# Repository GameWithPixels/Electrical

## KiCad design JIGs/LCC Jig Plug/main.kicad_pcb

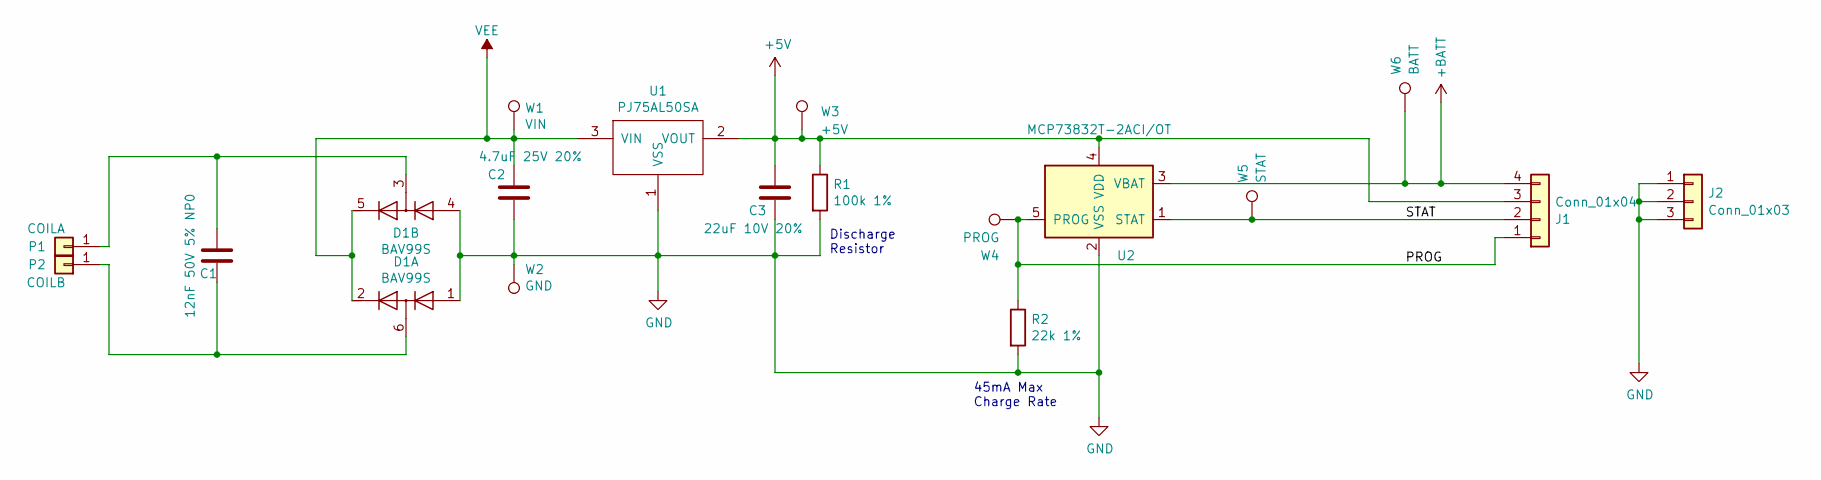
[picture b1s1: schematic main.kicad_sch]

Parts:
C1: 12nF 50V 5% NP0; C_0805_2012Metric; Manufacturer Part Number GRM2195C1H123JA01D; LCSC Part Number C97906
C2: 4.7uF 25V 20%; C_0603_1608Metric; Manufacturer Part Number GRM188R61E475KE11D; LCSC Part Number C90057
C3: 22uF 10V 20%; C_0603_1608Metric; Manufacturer Part Number GRM188R61A226ME15D; LCSC Part Number C84419
D1: BAV99S; SOT-363_SC-70-6; Manufacturer Part Number BAV99S,115; LCSC Part Number C96225
J1: Conn_01x04; PinHeader_1x04_P2.54mm_Vertical
J2: Conn_01x03; PinHeader_1x03_P2.54mm_Vertical
P1: COILA; TestPoint_THTPad_D1.5mm_Drill0.7mm
P2: COILB; TestPoint_THTPad_D1.5mm_Drill0.7mm
R1: 100k 1%; R_0402_1005Metric; Manufacturer Part Number 0402WGF1003TCE; LCSC Part Number C25741
R2: 22k 1%; R_0402_1005Metric; Manufacturer Part Number 0402WGF2202TCE; LCSC Part Number C25768
U1: PJ75AL50SA; SOT-23; Manufacturer Part Number PJ75AL50SA
U2: MCP73832T-2ACI/OT; SOT-23-5; Manufacturer Part Number MCP73832T-2ACI/OT; LCSC Part Number C38066
W1: VIN; TEST_PIN
W2: GND; TEST_PIN
W3: +5V; TEST_PIN
W4: PROG; TEST_PIN
W5: STAT; TEST_PIN
W6: BATT; TEST_PIN

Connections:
+5V: C3.1, J1.3, R1.1, U1.2 (VOUT), U2.4 (VDD), W3.1
+BATT: J1.4, U2.3 (VBAT), W6.1
/PROG: J1.1, R2.1, U2.5 (PROG), W4.1
/STAT: J1.2, U2.1 (STAT), W5.1
GND: C2.2, C3.2, D1.1 (A1), D1.4 (A3), J2.1, J2.2, J2.3, R1.2, R2.2, U1.1 (VSS), U2.2 (VSS), W2.1
unnamed: C1.2, D1.6 (K3A4), P2.1
unnamed: C1.1, D1.3 (K1A2), P1.1
VEE: C2.1, D1.2 (K2), D1.5 (K4), U1.3 (VIN), W1.1

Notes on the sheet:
Discharge Resistor
45mA Max Charge Rate

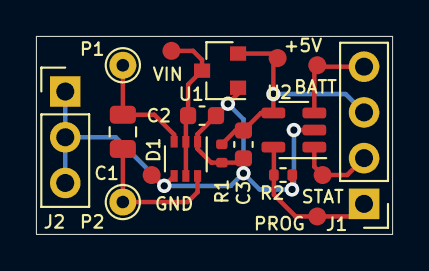
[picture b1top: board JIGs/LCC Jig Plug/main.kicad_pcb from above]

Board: 2 copper layers, 19.8 x 11.0 mm, 18 parts (0 on the bottom side), 8 nets.

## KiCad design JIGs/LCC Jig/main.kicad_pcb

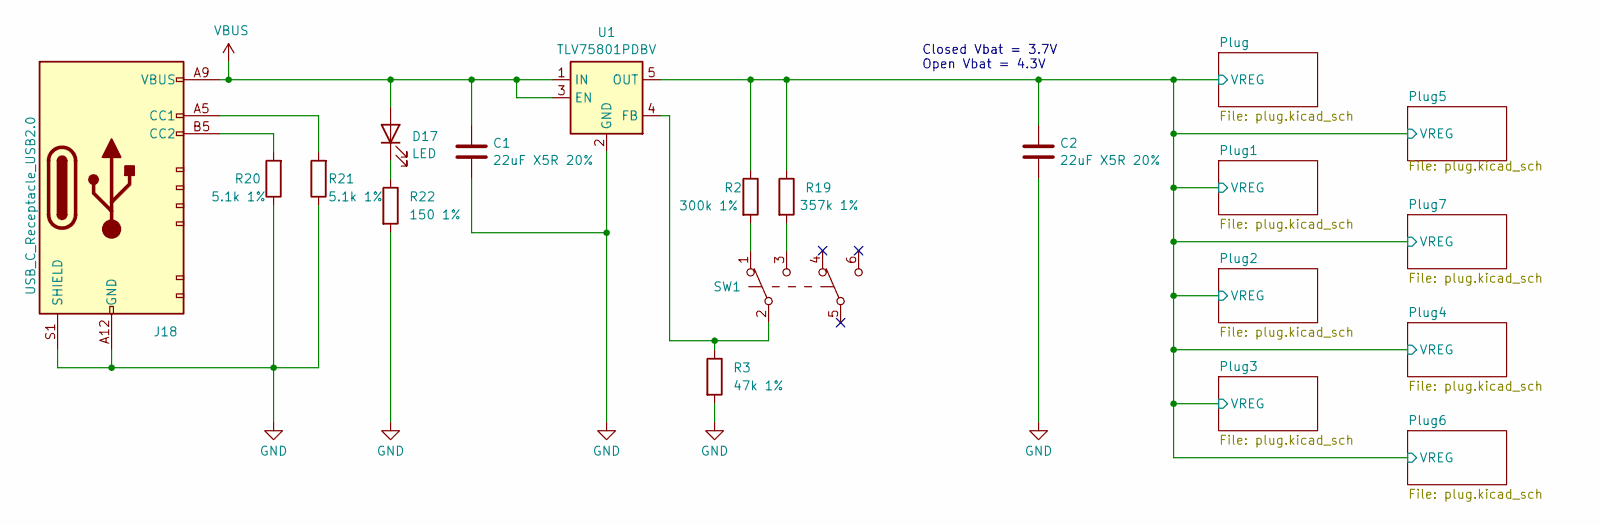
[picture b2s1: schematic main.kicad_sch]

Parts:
C1, C2: 22uF X5R 20%; C_0805_2012Metric; Part Number GRM21BR61E226ME44L; LCSC Part Number C86816
D17: LED; LED_0603_1608Metric; Part Number XL-1608UGC-04
J18: USB_C_Receptacle_USB2.0; USB-C-SMD_10P-P1.00-L6.8-W8.9; Part Number TYPE-C-31-M-17; LCSC Part Number C283540
R2: 300k 1%; R_0603_1608Metric; Part Number 0603WAF3003T5E
R3: 47k 1%; R_0603_1608Metric; Part Number 0603WAF4702T5E; LCSC Part Number C25819
R19: 357k 1%; R_0603_1608Metric; Part Number 0603WAF3573T5E
R20, R21: 5.1k 1%; R_0402_1005Metric; Part Number 0402WGF5101TCE; LCSC Part Number C25905
R22: 150 1%; R_0603_1608Metric; Part Number 0603WAF1500T5E; LCSC Part Number C22808
SW1: SW_Push_DPDT; XKB8080-W; Part Number XKB8080-W; LCSC Part Number C318861
U1: TLV75801PDBV; SOT-23-5; Part Number TLV75801PDBVR; LCSC Part Number C2877852

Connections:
/Plug/VREG: C2.1, R2.1, R19.1, U1.5 (OUT); also elsewhere on the board
GND: C1.2, C2.2, J18.A12 (GND), J18.B12 (GND), J18.S1 (SHIELD), R3.2, R20.1, R21.1, R22.2, U1.2 (GND); also elsewhere on the board
unnamed: D17.1 (K), R22.1
unnamed: J18.A5 (CC1), R21.2
unnamed: J18.B5 (CC2), R20.2
unnamed: R2.2, SW1.1 (A)
unnamed: R19.2, SW1.3 (C)
unnamed: R3.1, SW1.2 (B), U1.4 (FB)
VBUS: C1.1, D17.2 (A), J18.A9 (VBUS), J18.B9 (VBUS), U1.1 (IN), U1.3 (EN)

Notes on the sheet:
Closed Vbat = 3.7V Open Vbat = 4.3V

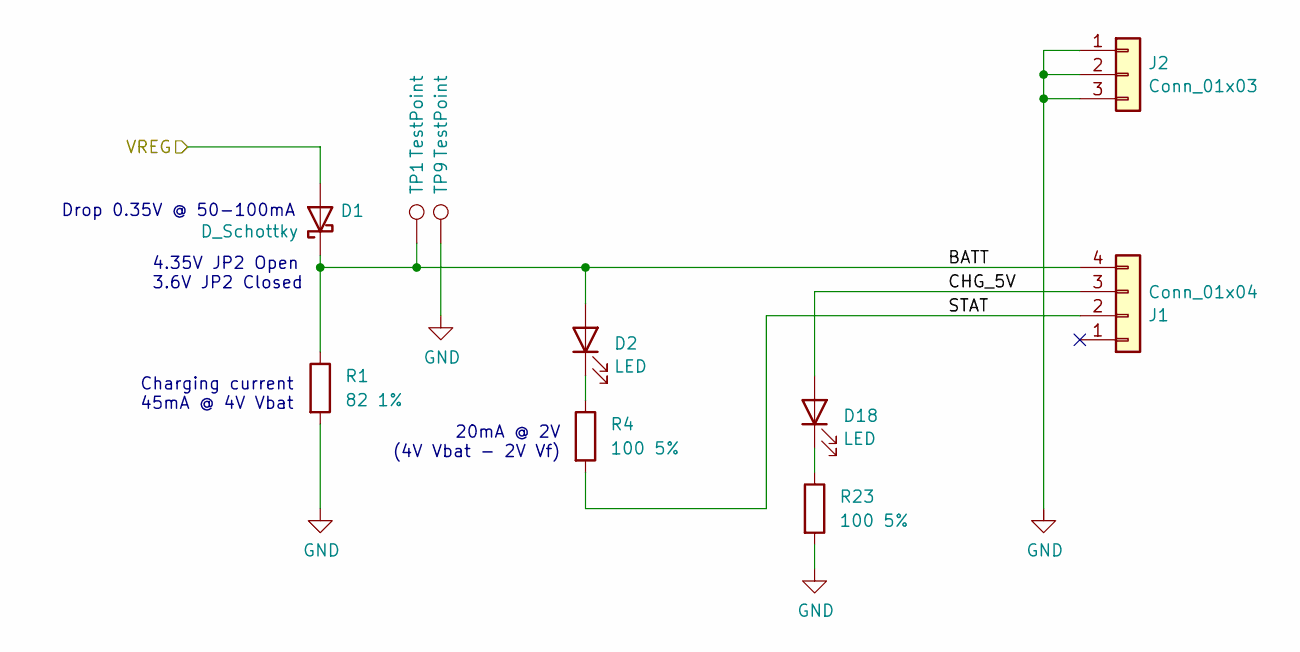
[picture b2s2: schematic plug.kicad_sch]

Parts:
D1: D_Schottky; D_SOD-523; Part Number RB521S30T1G; LCSC Part Number C145179
D2: LED; LED_0603_1608Metric; Part Number XL-1608SURC-06; LCSC Part Number C965799
D18: LED; LED_0603_1608Metric; Part Number XL-1608UOC-06
J1: Conn_01x04; PinSocket_1x04_P2.54mm_Vertical
J2: Conn_01x03; PinSocket_1x03_P2.54mm_Vertical
R1: 82 1%; R_1210_3225Metric; Part Number RC1210JR-0782RL; LCSC Part Number C728413
R4, R23: 100 5%; R_0603_1608Metric; Part Number 0603WAJ0101T5E; LCSC Part Number C25201
TP1, TP9: TestPoint; PinHeader_1x01_P2.54mm_Vertical

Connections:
/Plug/BATT: D1.1 (K), D2.2 (A), J1.4, R1.1, TP1.1
/Plug/CHG_5V: D18.2 (A), J1.3
/Plug/STAT: J1.2, R4.2
/Plug/VREG: D1.2 (A); also elsewhere on the board
GND: J2.1, J2.2, J2.3, R1.2, R23.2; also elsewhere on the board
unnamed: D2.1 (K), R4.1
unnamed: D18.1 (K), R23.1

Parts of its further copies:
D3, D5, D7, D9, D11, D13, D15: D_Schottky; D_SOD-523; Part Number RB521S30T1G; LCSC Part Number C145179
D4, D6, D8, D10, D12, D14, D16: LED; LED_0603_1608Metric; Part Number XL-1608SURC-06; LCSC Part Number C965799
D19, D20, D21, D22, D23, D24, D25: LED; LED_0603_1608Metric; Part Number XL-1608UOC-06
J3, J5, J7, J9, J11, J13, J15: Conn_01x04; PinSocket_1x04_P2.54mm_Vertical
J4, J6, J8, J10, J12, J14, J16: Conn_01x03; PinSocket_1x03_P2.54mm_Vertical
R5, R7, R9, R11, R13, R15, R17: 82 1%; R_1210_3225Metric; Part Number RC1210JR-0782RL; LCSC Part Number C728413
R6, R8, R10, R12, R14, R16, R18, R24, R25, R26, R27, R28, R29, R30: 100 5%; R_0603_1608Metric; Part Number 0603WAJ0101T5E; LCSC Part Number C25201
TP10: TestPoint; PinHeader_1x01_P2.54mm_Vertical

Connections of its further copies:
/Plug1/BATT: D3.1 (K), D4.2 (A), J3.4, R5.1
/Plug1/CHG_5V: D19.2 (A), J3.3
/Plug1/STAT: J3.2, R6.2
/Plug2/BATT: D5.1 (K), D6.2 (A), J5.4, R7.1
/Plug2/CHG_5V: D20.2 (A), J5.3
/Plug2/STAT: J5.2, R8.2
/Plug3/BATT: D7.1 (K), D8.2 (A), J7.4, R9.1
/Plug3/CHG_5V: D21.2 (A), J7.3
/Plug3/STAT: J7.2, R10.2
/Plug4/BATT: D13.1 (K), D14.2 (A), J13.4, R15.1
/Plug4/CHG_5V: D24.2 (A), J13.3
/Plug4/STAT: J13.2, R16.2
/Plug5/BATT: D9.1 (K), D10.2 (A), J9.4, R11.1
/Plug5/CHG_5V: D22.2 (A), J9.3
/Plug5/STAT: J9.2, R12.2
/Plug6/BATT: D15.1 (K), D16.2 (A), J15.4, R17.1
/Plug6/CHG_5V: D25.2 (A), J15.3
/Plug6/STAT: J15.2, R18.2
/Plug7/BATT: D11.1 (K), D12.2 (A), J11.4, R13.1
/Plug7/CHG_5V: D23.2 (A), J11.3
/Plug7/STAT: J11.2, R14.2
/Plug/VREG: D3.2 (A), D5.2 (A), D7.2 (A), D9.2 (A), D11.2 (A), D13.2 (A), D15.2 (A); also elsewhere on the board
GND: J4.1, J4.2, J4.3, J6.1, J6.2, J6.3, J8.1, J8.2, J8.3, J10.1, J10.2, J10.3, J12.1, J12.2, J12.3, J14.1, J14.2, J14.3, J16.1, J16.2, J16.3, R5.2, R7.2, R9.2, R11.2, R13.2, R15.2, R17.2, R24.2, R25.2, R26.2, R27.2, R28.2, R29.2, R30.2, TP10.1; also elsewhere on the board
unnamed: D4.1 (K), R6.1
unnamed: D6.1 (K), R8.1
unnamed: D8.1 (K), R10.1
unnamed: D10.1 (K), R12.1
unnamed: D12.1 (K), R14.1
unnamed: D14.1 (K), R16.1
unnamed: D16.1 (K), R18.1
unnamed: D19.1 (K), R24.1
unnamed: D20.1 (K), R25.1
unnamed: D21.1 (K), R26.1
unnamed: D22.1 (K), R27.1
unnamed: D23.1 (K), R28.1
unnamed: D24.1 (K), R29.1
unnamed: D25.1 (K), R30.1

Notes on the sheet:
20mA @ 2V (4V Vbat - 2V Vf)
4.35V JP2 Open 3.6V JP2 Closed
Charging current 45mA @ 4V Vbat
Drop 0.35V @ 50-100mA

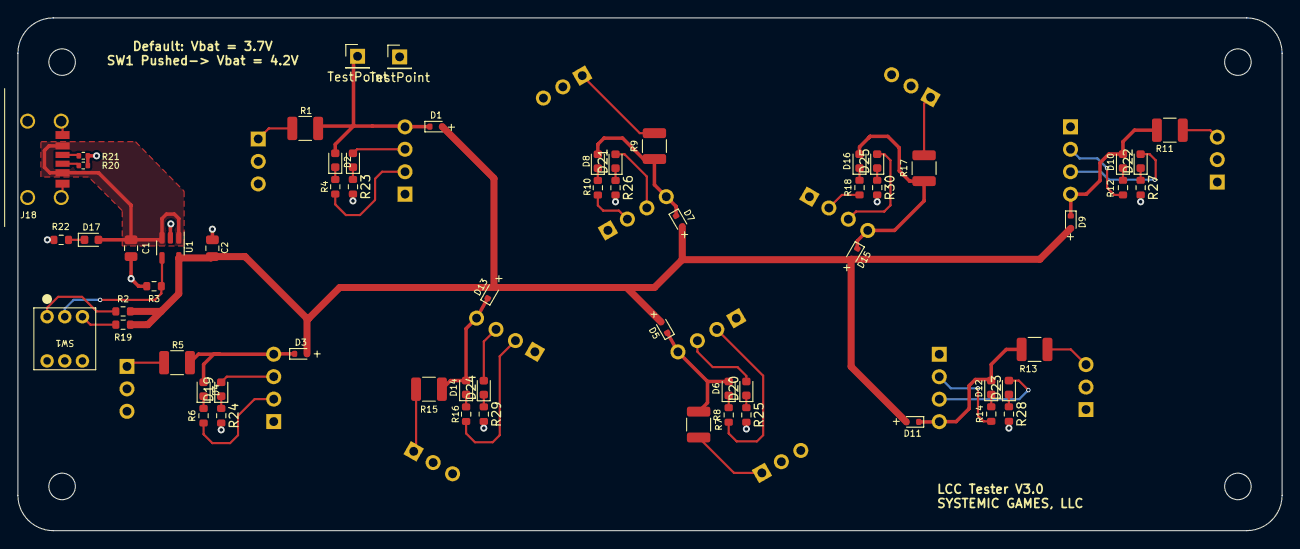
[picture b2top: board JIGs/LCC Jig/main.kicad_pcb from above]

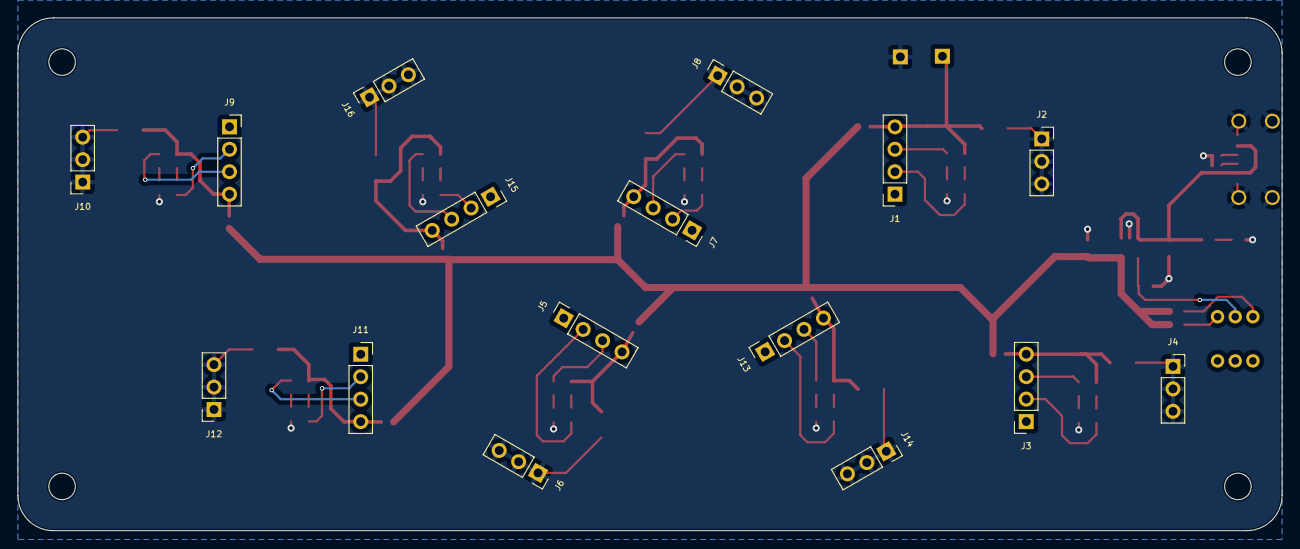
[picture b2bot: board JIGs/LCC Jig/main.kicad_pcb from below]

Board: 2 copper layers, 143.0 x 58.0 mm, 78 parts (16 on the bottom side), 49 nets.

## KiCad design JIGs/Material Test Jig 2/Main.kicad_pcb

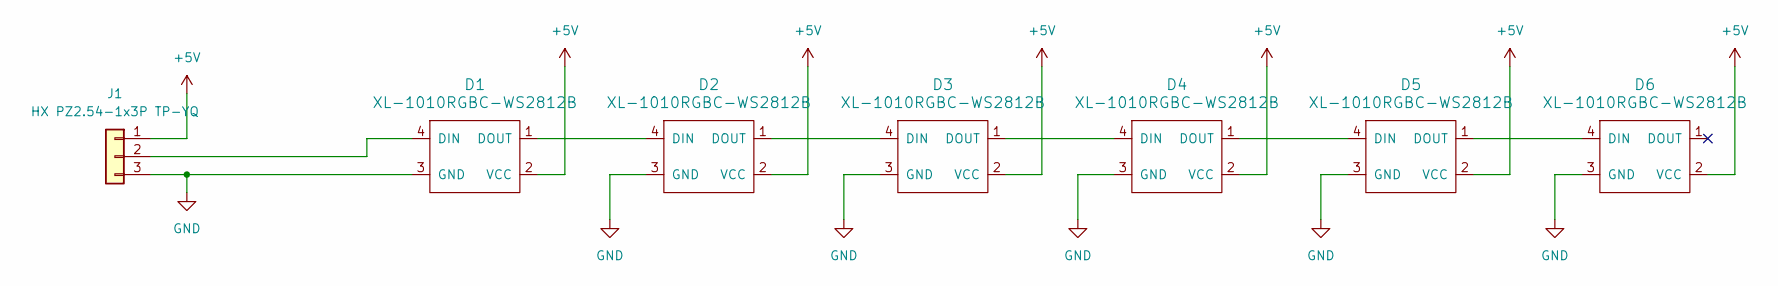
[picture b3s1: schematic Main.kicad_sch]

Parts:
D1, D2, D3, D4, D5, D6: XL-1010RGBC-WS2812B
J1: HX PZ2.54-1x3P TP-YQ; PinHeader_1x03_P2.54mm_Vertical_SMD_Pin1Left

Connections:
+5V: D1.2 (VCC), D2.2 (VCC), D3.2 (VCC), D4.2 (VCC), D5.2 (VCC), D6.2 (VCC), J1.1
GND: D1.3 (GND), D2.3 (GND), D3.3 (GND), D4.3 (GND), D5.3 (GND), D6.3 (GND), J1.3
unnamed: D1.4 (DIN), J1.2
unnamed: D1.1 (DOUT), D2.4 (DIN)
unnamed: D2.1 (DOUT), D3.4 (DIN)
unnamed: D3.1 (DOUT), D4.4 (DIN)
unnamed: D4.1 (DOUT), D5.4 (DIN)
unnamed: D5.1 (DOUT), D6.4 (DIN)

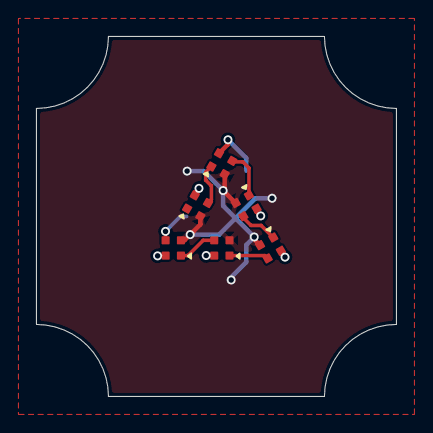
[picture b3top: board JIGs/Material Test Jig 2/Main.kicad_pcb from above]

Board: 2 copper layers, 20.0 x 20.0 mm, 7 parts (1 on the bottom side), 8 nets.
